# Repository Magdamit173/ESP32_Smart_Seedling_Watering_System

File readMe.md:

# ESP32-Based Smart Seedling Watering System with Automated Environmental Control

A low-cost, locally controlled seedling watering prototype designed to reduce repetitive manual watering while combining embedded programming, environmental sensing, real-time scheduling, relay/solenoid control, fluid delivery, and mechanical fabrication.

> **Project:** Midterm Project #1  
> **Course:** Microprocessors, Microcontroller Systems and Design  
> **Author:** Rovic B. Magdamit  
> **Institution:** University of Caloocan City – College of Engineering

## Overview

The system automates watering for a small seedling tray using an **ESP32-C3** as the central controller. It uses a **DHT22/AM2302** for temperature and relative-humidity monitoring and a **DS3231 RTC** for the time reference required by daily watering schedules.

A phone or laptop connects directly to the ESP32's local Wi-Fi access point and opens the controller's web interface. No cloud service or external router is required.

The final prototype uses a gravity-fed water path:

```text
~10-L Reservoir
      │
      ▼
 Clear Tubing
      │
      ▼
 Solenoid Valve
      │
      ▼
 Water Outlet
      │
      ▼
 Seedling Tray
```

The electrical/control path is:

```text
DHT22 ───────────────┐
                     │
DS3231 ──────────────┤
                     ▼
                ESP32-C3
                     │
              Control Logic
                     │
                     ▼
              Transistor/Relay
                     │
                     ▼
               Solenoid Valve
```

## Main Features

- Daily scheduled watering using the DS3231 RTC
- Configurable temperature and relative-humidity rules
- Optional second environmental condition using **AND** or **OR**
- Configurable persistence period before an environmental rule can trigger watering
- Cooldown period to reduce repeated environmental triggering
- Wireless manual watering
- Wireless force-stop watering
- Hard software watering limit of **30 minutes**
- Non-blocking `millis()` timing for watering duration, sensor polling, persistence, and cooldown
- Local Wi-Fi SoftAP + HTTP web interface
- Configuration stored in ESP32 non-volatile storage using `Preferences`
- Connected devices can retrieve the ESP32's stored schedules and environmental rules
- DS3231 retains the time reference when the ESP32 is unpowered
- Relay and solenoid inductive-load protection using flyback diodes

## Hardware

### Controller

| Component | Function |
|---|---|
| ESP32-C3 SuperMini | Main controller, Wi-Fi access point, web server |
| DHT22 / AM2302 | Temperature and relative-humidity sensing |
| DS3231 RTC | Time-of-day reference for scheduled watering |
| SRD-05VDC-SL-C relay | Electrical isolation/switching for watering actuator |
| PN2222A transistor drivers | Relay/actuator driver stage |
| LM7805 | 5 V regulation |
| Flyback diodes | Inductive-load protection |
| LED indicator | Visual status indication |
| DC barrel jack | External power input |
| Terminal blocks / headers | Wiring connections |

### Watering and Structure

- Approximately 10-L plastic reservoir
- Clear tubing
- DC solenoid valve
- Seedling tray
- Blue PVC pipe
- PVC elbow and tee fittings
- Nylon rope for reservoir/outlet support
- Clear acrylic electronics enclosure
- Acrylic adhesive

## ESP32-C3 Pin Assignment

| ESP32-C3 Pin | Assignment | Function |
|---|---|---|
| GPIO4 | `DHT_PIN` | DHT22 / AM2302 data |
| GPIO5 | `WATER_PIN` | Relay/transistor watering control |
| GPIO6 | `RTC_SDA` | DS3231 SDA |
| GPIO7 | `RTC_SCL` | DS3231 SCL |
| I2C `0x68` | DS3231 | RTC device address |
| `192.168.4.1` | Wi-Fi AP | Local HTTP configuration interface |

## Power Arrangement

The prototype uses a **12 V DC input** before regulation.

The controller uses a regulated **5 V rail** for the low-voltage electronics and compatible actuator/control circuitry.

The solenoid is controlled through the relay/transistor stage rather than directly from an ESP32 GPIO.

> The external adapter's current rating is a maximum available capacity; the connected load draws the current required by the circuit.

## Software Architecture

The firmware runs as a continuously serviced control loop.

The major tasks are:

1. Service the local HTTP server.
2. Read the DHT22 at the configured sensor interval.
3. Read the DS3231 for calendar/time-of-day information.
4. Evaluate scheduled watering events.
5. Evaluate environmental rules.
6. Control the relay/solenoid watering output.
7. Enforce watering duration and safety limits.
8. Save/retrieve controller configuration through non-volatile storage.

### Non-Blocking Timing

Watering is intentionally not implemented as a long `delay()` operation.

When watering begins, the firmware records the starting value of `millis()` and checks elapsed time on later loop iterations.

The same approach is used for:

- watering duration
- environmental persistence
- cooldown
- sensor polling

This allows the ESP32 to continue servicing the web interface and other controller tasks while watering is active.

## Scheduling and Environmental Rules

### Scheduled Watering

A scheduled event contains:

- time of day
- watering duration
- enable state

The DS3231 provides the calendar-time reference used to determine when a daily event is due.

### Environmental Watering

An environmental rule can use:

- temperature or relative humidity
- comparison operator
- threshold
- optional second condition
- `AND` / `OR` logic
- persistence period
- watering duration
- cooldown

For example, a rule can conceptually be configured as:

```text
IF temperature > threshold
AND the condition remains true for the persistence period
THEN water for the configured duration
AND wait for the cooldown before another trigger
```

The system does **not** claim that one watering amount is correct for every plant. Watering duration is configurable because plant type, tray geometry, substrate, age, temperature, and humidity can change actual water requirements.

## Local Web Interface

The ESP32 creates its own local Wi-Fi network:

```text
SSID: ESP32_Smart_Seedling_Waterer
IP:   192.168.4.1
```

A connected phone or laptop can use the browser interface for:

- schedule configuration
- temperature/humidity rule configuration
- automation control
- manual watering
- force stop
- controller status monitoring
- retrieving the stored configuration

The ESP32's **non-volatile configuration is the shared source of truth**, while browser `localStorage` acts as a local editing copy. This allows a newly connected device to retrieve the current configuration instead of depending on the settings stored only in one browser.

## RTC Operation

The DS3231 is used specifically for **time-of-day scheduling**.

The distinction between the DS3231 and `millis()` is important:

- `millis()` measures elapsed time only while the ESP32 is running.
- The DS3231 provides the calendar/time reference for daily schedules and retains the clock when the ESP32 is unpowered.

The RTC was verified during development using an I2C scanner and a focused RTClib test. The DS3231 appeared at:

```text
0x68
```

The other observed I2C device at `0x57` was present during the scanner test but was not used as the RTC device.

## Fluid-System Design

The final prototype is **gravity-fed** and does not use a separate pump.

The water surface is elevated above the valve/outlet, creating hydrostatic head:

\[
P = \rho g h
\]

where:

- \(P\) = hydrostatic pressure contribution
- \(\rho\) = water density
- \(g\) = gravitational acceleration
- \(h\) = vertical water head

As an illustrative reference, a **9-inch vertical water head**:

```text
9 in = 0.2286 m
```

corresponds to approximately:

```text
2.24 kPa
≈ 0.33 psi
```

This is a reference calculation based on elevation difference, not a measured pressure value for every reservoir fill condition.

Actual flow depends on:

- reservoir water level
- valve elevation
- tubing resistance
- valve orifice
- fitting losses
- outlet geometry

The selected low/zero-differential-pressure solenoid arrangement is therefore appropriate for a gravity-fed concept where a conventional pressure-driven valve may not operate correctly at very low available pressure.

## Structural Design

The physical support structure uses blue PVC pipe with elbow and tee fittings.

The main square members are approximately:

```text
9 in × 9 in
```

with additional short and diagonal members used for support and bracing.

The structure supports:

- the reservoir
- the watering outlet
- the tubing
- the seedling tray area

The reservoir was based on an approximately **10-L container**. Water alone has an approximate mass of:

```text
10 kg
```

and an approximate weight of:

```text
W = mg
  ≈ 98.1 N
```

The nylon rope attachment points distribute the hanging load into the PVC support structure. Actual rope tension depends on attachment geometry and load distribution, so the prototype is considered a demonstration structure rather than a rated lifting frame.

The PVC joints were assembled without additional sealant because the fitted prototype was sufficiently rigid for the intended demonstration.

## Electronics Enclosure

The controller electronics were assembled inside a small clear acrylic enclosure.

The enclosure accommodates:

- controller board
- relay/driver circuitry
- wiring
- power input
- manual controls
- actuator connections

The enclosure was fabricated as a practical prototype rather than a production enclosure. Visible adhesive and cable management reflect the iterative construction process.

## Development and Iteration

The project was developed through repeated testing and redesign rather than a single build sequence.

### 1. Initial Mechanical Concept

The earliest concept involved transporting a seedling tray through a watering zone using a conveyor.

The concept was eventually abandoned because the added requirements for:

- motor control
- guides
- entry/exit sensing
- mechanical timing
- additional fabrication

made the system unnecessarily complex for the available prototype resources.

The final design retained the programmable watering concept but changed to a stationary seedling watering structure.

### 2. Wireless Communication

Bluetooth Low Energy was attempted first.

The prototype repeatedly experienced connection/disconnection behavior and browser GATT service retrieval failures. The communication design was therefore changed to **ESP32 SoftAP Wi-Fi + HTTP**, which preserved local wireless operation while simplifying browser interaction.

### 3. RTC Debugging

The main program initially reported the DS3231 as not detected even though the eventual hardware connection was correct.

An I2C scanner identified:

```text
0x57
0x68
```

A focused RTClib test then detected the DS3231 at `0x68` and returned a readable time.

### 4. Configuration Synchronization

The web interface initially did not consistently reconstruct schedules and environmental rules across different connected devices.

The final approach stores the configuration on the ESP32 using non-volatile storage. The browser maintains a local editing copy, while the ESP32 remains the authoritative stored configuration.

## Safety and Reliability

The prototype includes several protections and reliability measures:

- 30-minute maximum watering duration
- dedicated force-stop command
- relay coil flyback protection
- solenoid inductive-load flyback protection
- transistor drivers between control logic and actuator circuitry
- independent DS3231 time reference
- non-blocking elapsed-time logic
- non-volatile configuration storage
- low-pressure gravity-fed watering arrangement

The system is intended as a low-cost educational prototype, not a certified agricultural or load-bearing product.

## Estimated Project Cost

The documented/estimated project cost is approximately:

```text
₱1,235
```

This includes recorded purchase prices, approximate prices for unpriced components, an estimated **₱30** for three 2-pin terminal blocks, and a **₱300 miscellaneous/catch-up allowance** for solder, small parts, and other unpriced consumables.

The figure represents best-effort prototype spending rather than an exact manufacturing cost for a production unit.

## Project Status

The completed prototype demonstrates integrated operation of:

- embedded control
- environmental sensing
- real-time scheduling
- local wireless configuration
- relay/solenoid actuation
- gravity-fed water delivery
- PVC structural support
- acrylic electronics enclosure

The strongest result of the project is the integration of these subsystems into one functional prototype.

## Repository Contents

The repository contains the complete implementation and supporting project resources.

The full firmware and project files are maintained here so the complete source does not need to be reproduced in the printed project documentation.

## Author

**Rovic B. Magdamit**  
ECE - 3A  
University of Caloocan City  
College of Engineering  
Electronics Engineering Department

## Project Title

**ESP32-Based Smart Seedling Watering System with Automated Environmental Control**

## License

No software license has been specified yet. Unless a license is added to this repository, the project should be treated as the author's project work and reused according to the repository owner's permission.

## AI-Assisted Development

AI tools were used as development assistants for brainstorming, debugging, code review, technical writing, and documentation. Final implementation, hardware construction, testing, and project decisions were performed and verified by the author.

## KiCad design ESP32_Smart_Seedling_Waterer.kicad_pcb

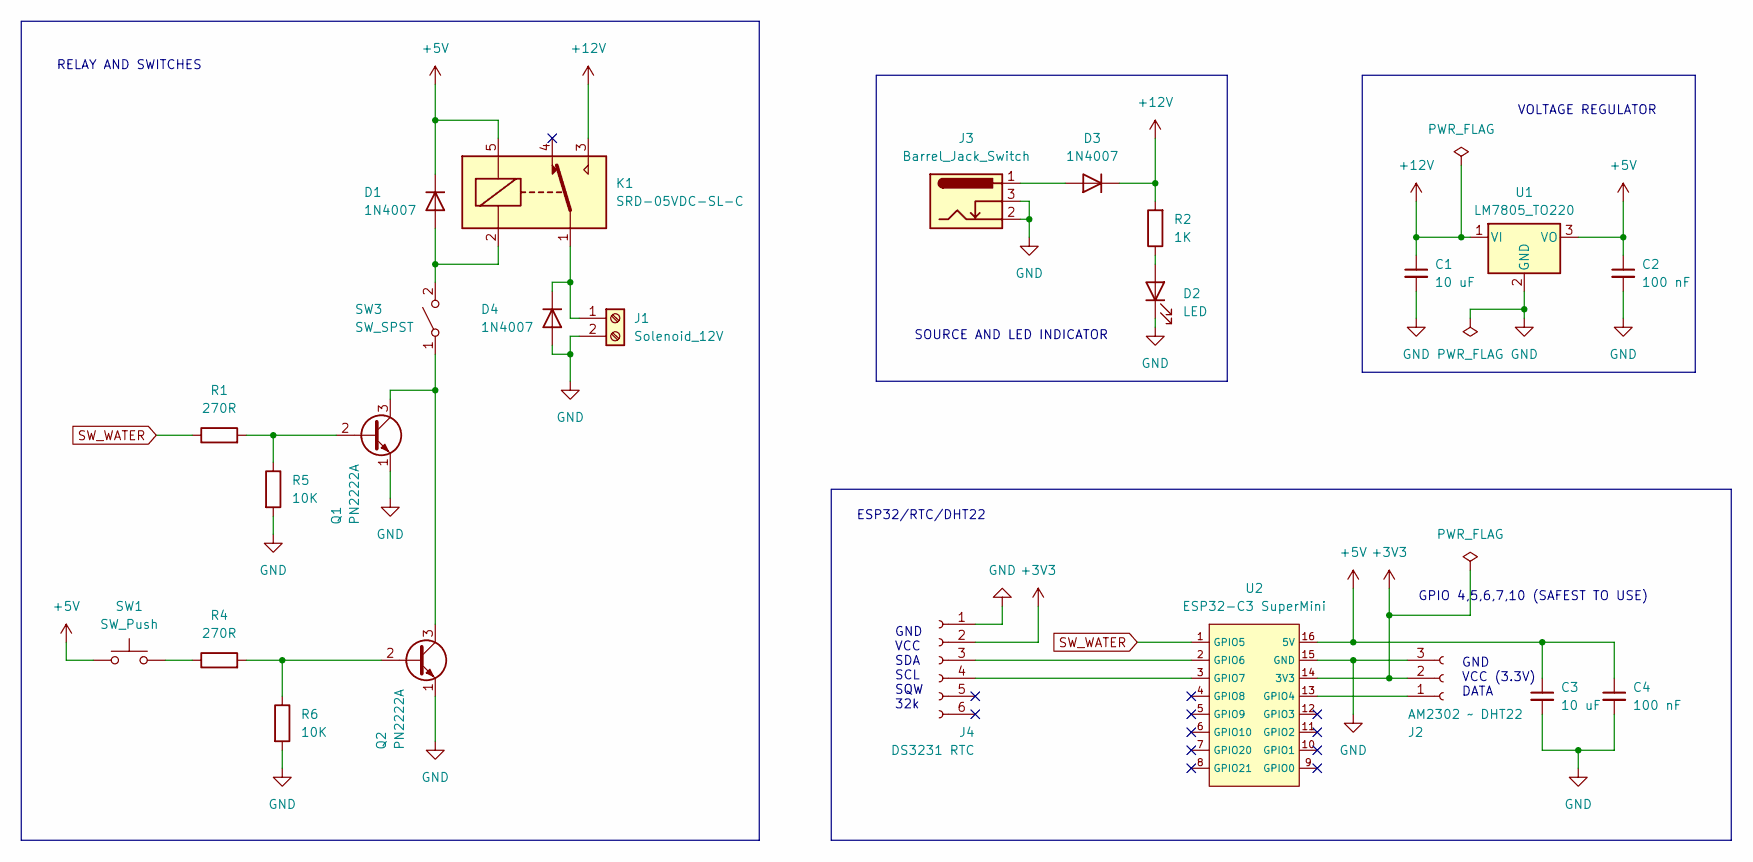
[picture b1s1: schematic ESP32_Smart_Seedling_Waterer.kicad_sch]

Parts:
C1, C3: 10 uF; C_Disc_D5.0mm_W2.5mm_P5.00mm
C2, C4: 100 nF; C_Disc_D5.0mm_W2.5mm_P5.00mm
D1, D3, D4: 1N4007; D_DO-41_SOD81_P10.16mm_Horizontal
D2: LED; LED_D5.0mm
J1: Solenoid_12V; TerminalBlock_Phoenix_MKDS-1,5-2_1x02_P5.00mm_Horizontal
J2: AM2302 ~ DHT22; PinSocket_1x03_P2.54mm_Vertical
J3: Barrel_Jack_Switch; BarrelJack_GCT_DCJ200-10-A_Horizontal
J4: DS3231 RTC; PinSocket_1x06_P2.54mm_Vertical
K1: SRD-05VDC-SL-C; Relay_SPDT_SANYOU_SRD_Series_Form_C
Q1, Q2: PN2222A; TO-92_HandSolder
R1, R4: 270R; R_Axial_DIN0207_L6.3mm_D2.5mm_P10.16mm_Horizontal
R2: 1K; R_Axial_DIN0207_L6.3mm_D2.5mm_P10.16mm_Horizontal
R5, R6: 10K; R_Axial_DIN0207_L6.3mm_D2.5mm_P10.16mm_Horizontal
SW1: SW_Push; TerminalBlock_Phoenix_MKDS-1,5-2_1x02_P5.00mm_Horizontal
SW3: SW_SPST; TerminalBlock_Phoenix_MKDS-1,5-2_1x02_P5.00mm_Horizontal
U1: LM7805_TO220; TO-220-3_Horizontal_TabDown
U2: ESP32-C3 SuperMini

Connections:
+3V3: J2.2, J4.2, U2.14 (3V3)
+5V: C2.1, C3.1, C4.1, D1.1 (K), K1.5, SW1.1, U1.3 (VO), U2.16 (5V)
+12V: C1.1, D3.1 (K), K1.3, R2.2, U1.1 (VI)
GND: C1.2, C2.2, C3.2, C4.2, D2.1 (K), D4.2 (A), J1.2, J2.3, J3.2, J3.3, J4.1, Q1.1 (E), Q2.1 (E), R5.2, R6.2, U1.2 (GND), U2.15 (GND)
unnamed: D1.2 (A), K1.2, SW3.2 (B)
unnamed: D2.2 (A), R2.1
unnamed: D3.2 (A), J3.1
unnamed: D4.1 (K), J1.1, K1.1
unnamed: J2.1, U2.13 (GPIO4)
unnamed: J4.3, U2.2 (GPIO6)
unnamed: J4.4, U2.3 (GPIO7)
unnamed: Q1.2 (B), R1.2, R5.1
unnamed: Q1.3 (C), Q2.3 (C), SW3.1 (A)
unnamed: Q2.2 (B), R4.2, R6.1
unnamed: R4.1, SW1.2
SW_WATER: R1.1, U2.1 (GPIO5)

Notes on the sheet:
VOLTAGE REGULATOR
SOURCE AND LED INDICATOR
RELAY AND SWITCHES
GND VCC SDA SCL SQW 32k
GPIO 4,5,6,7,10 (SAFEST TO USE)
GND VCC (3.3V) DATA
ESP32/RTC/DHT22

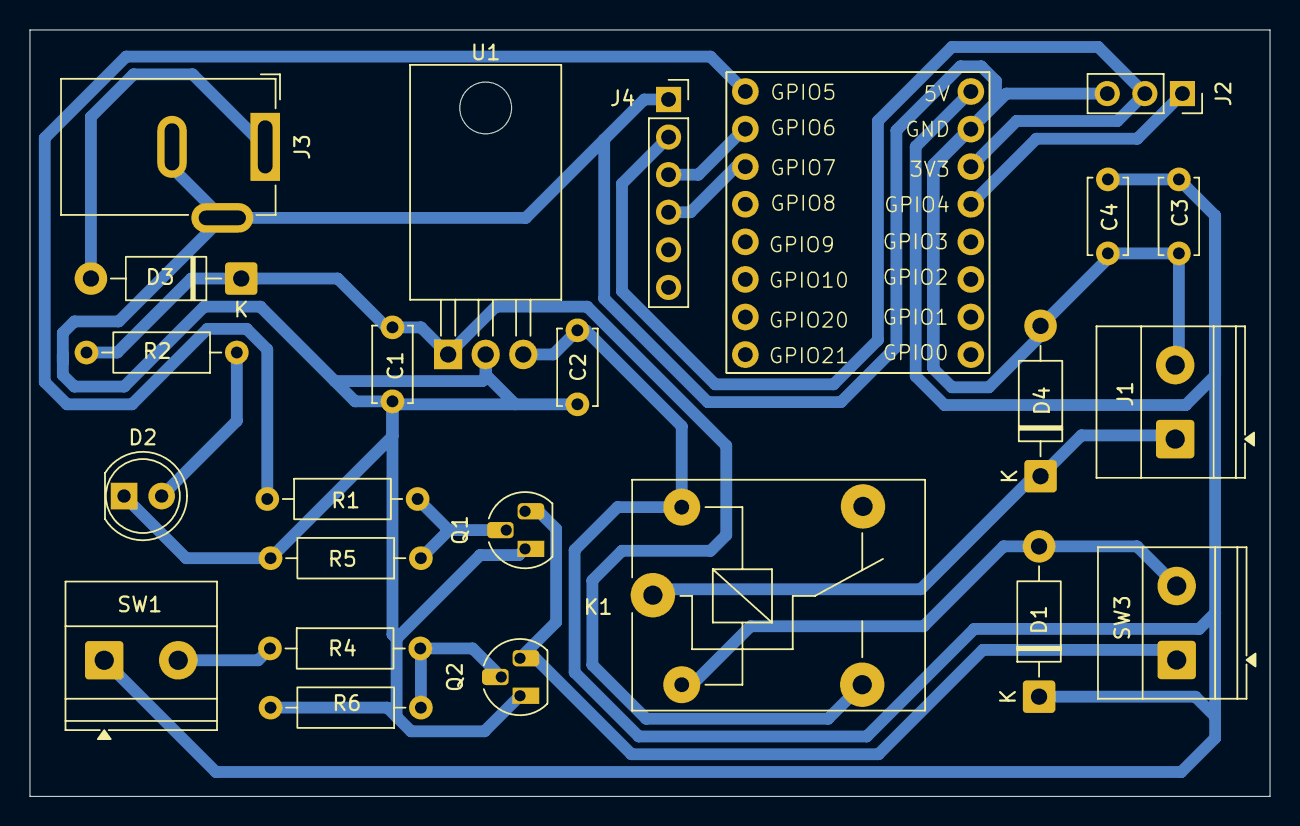
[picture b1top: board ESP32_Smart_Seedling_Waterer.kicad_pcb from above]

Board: 2 copper layers, 83.8 x 51.8 mm, 24 parts (0 on the bottom side), 16 nets.
